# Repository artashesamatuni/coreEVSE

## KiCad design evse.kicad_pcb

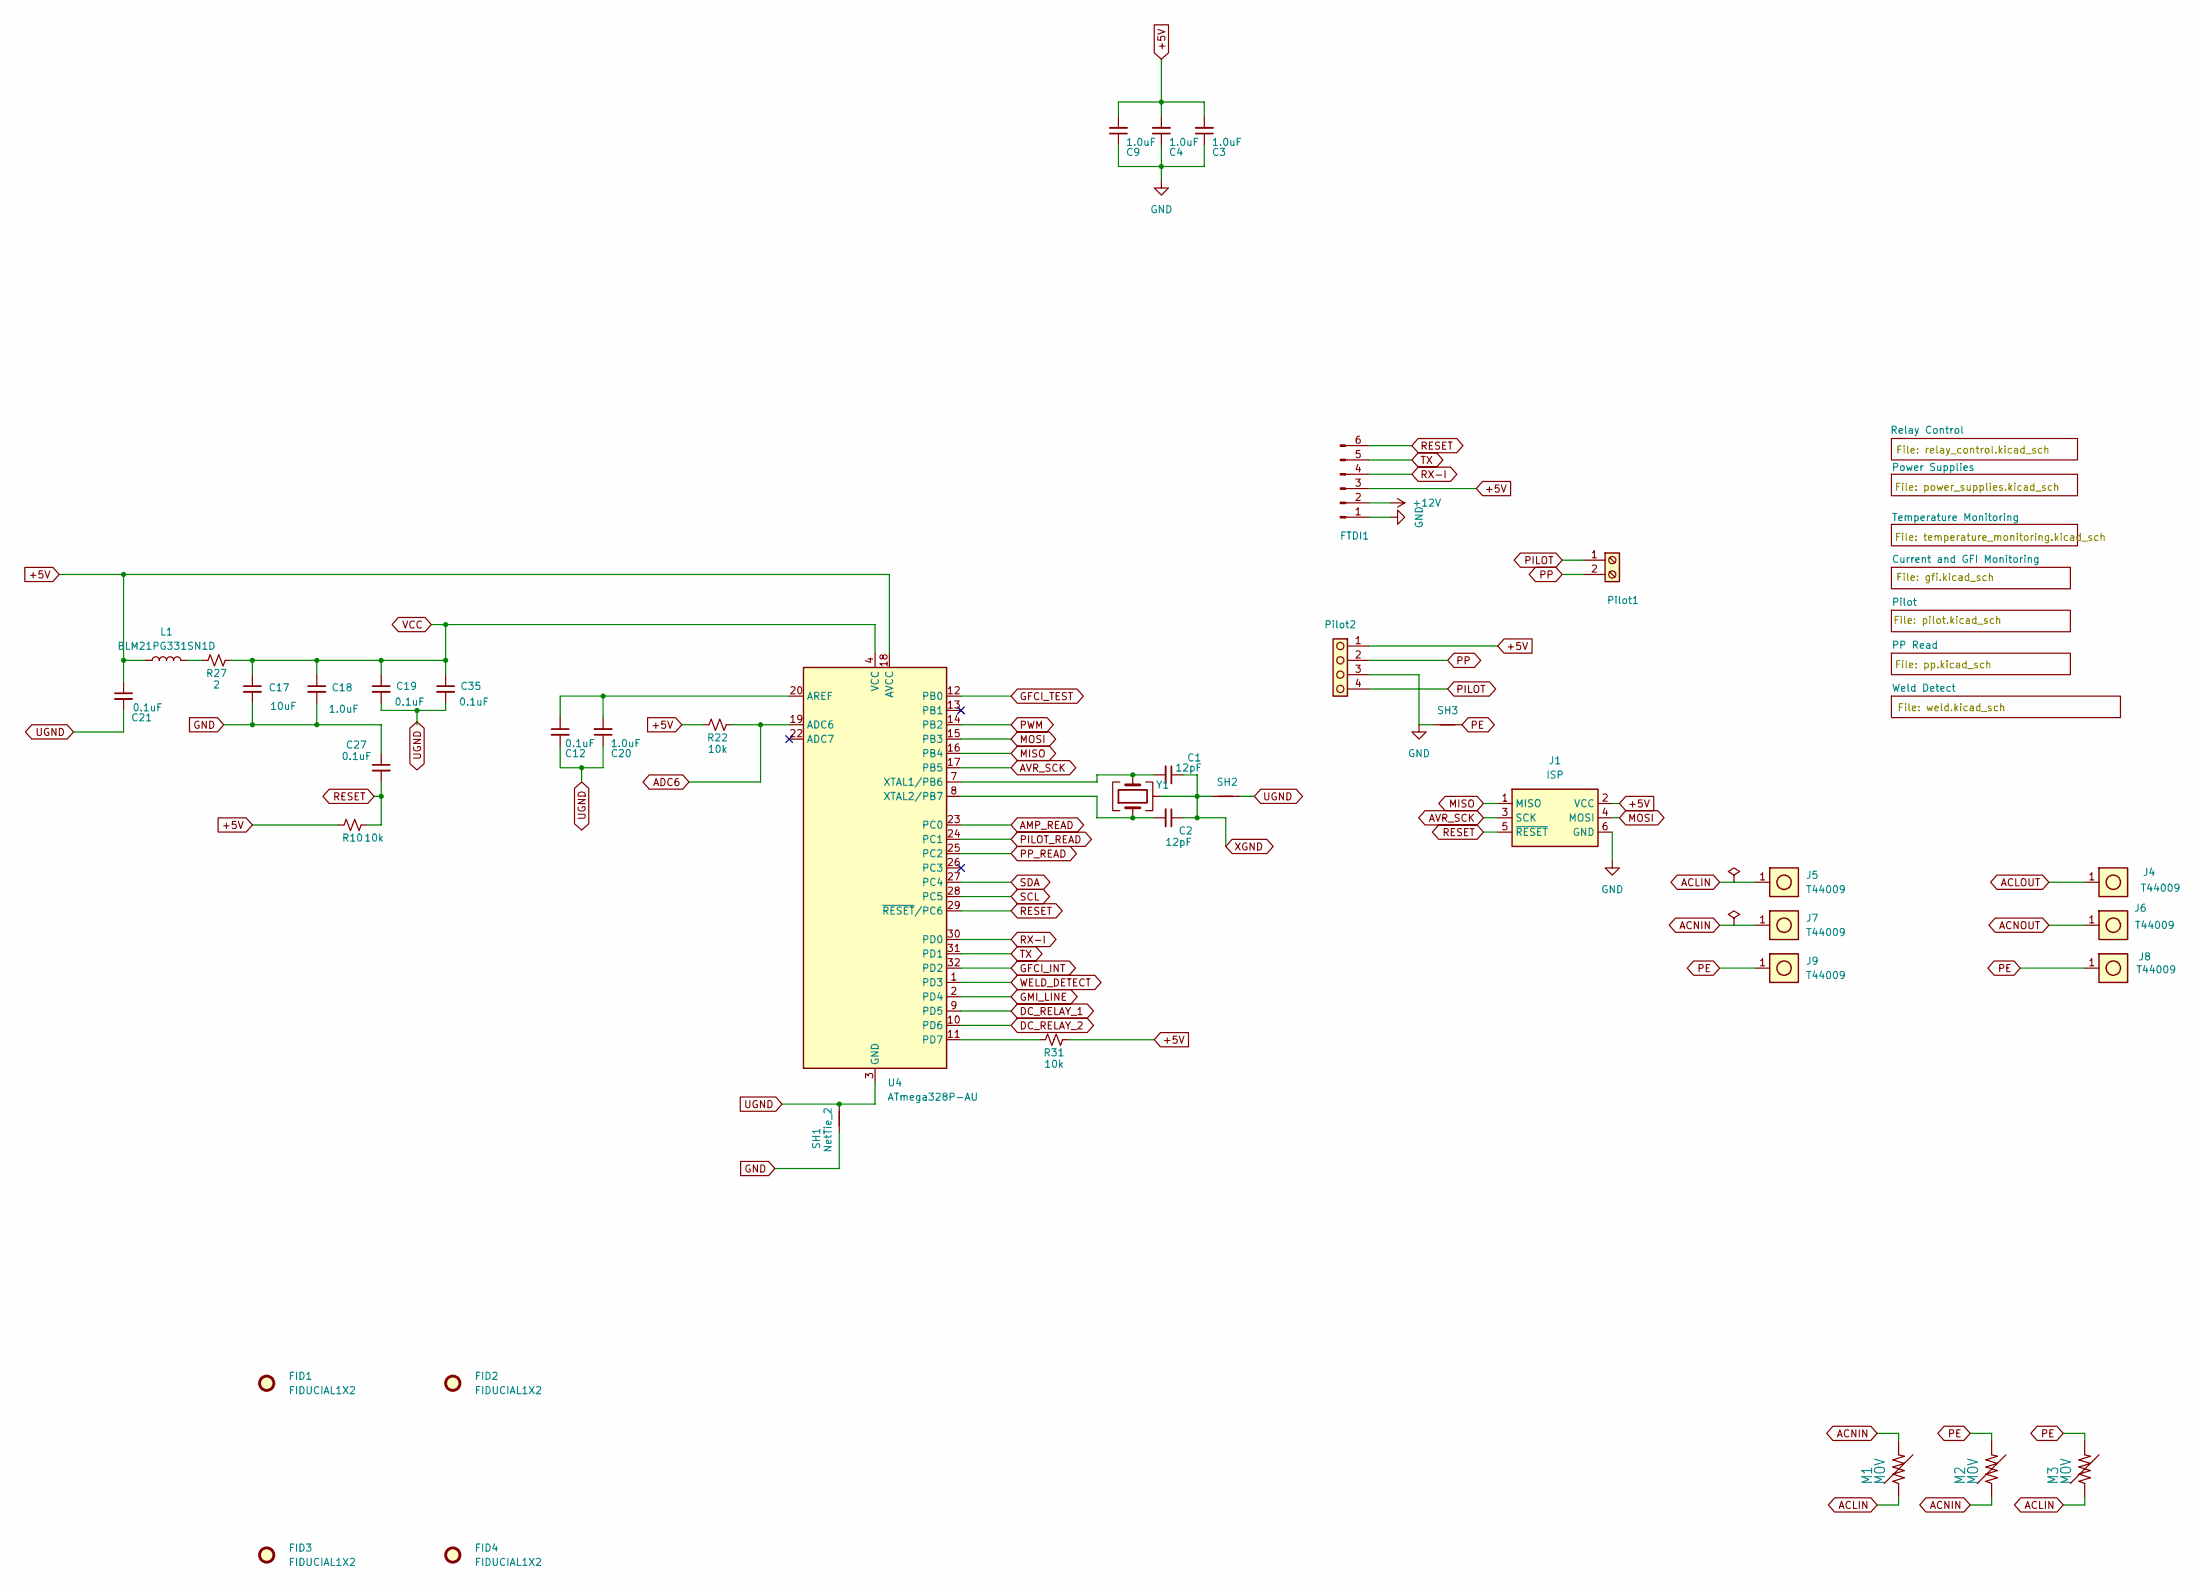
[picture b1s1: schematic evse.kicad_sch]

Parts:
C1, C2: 12pF; C_0402_1005Metric; Voltage 50V; Tolerance 2%; LCSC C696888
C3, C4, C9, C20: 1.0uF; C_0805_2012Metric; Voltage 25V; Tolerance 10%; LCSC C3848979
C12, C19, C21, C27: 0.1uF; C_0805_2012Metric; Voltage 25V; Tolerance 10%; LCSC C129641
C17: 10uF; C_0603_1608Metric_Polar; Voltage 10V; Tolerance 20%
C18: 1.0uF; C_0201_0603Metric; Voltage 25V; Tolerance 10%
C35: 0.1uF; C_0402_1005Metric; Voltage 25V; Tolerance 10%; LCSC C169842
FID1, FID2, FID3, FID4: FIDUCIAL1X2; Fiducial_1mm_Mask2mm
FTDI1: Conn_01x06_Pin; FTDI_JST_PH_1x06_P2.00mm
J1: ISP; AVR_ISP_2x03_P2.54mm
J4, J5, J6, J7, J8, J9: T44009; Terminal_T44009_M4
L1: BLM21PG331SN1D; L_0805_2012Metric; LCSC C74764
M1, M2, M3: MOV
Pilot1: KF128-2.54-2P; TerminalBlock_KF128-2.54-2P; LCSC C474920
Pilot2: KF128-2.54-4P; TerminalBlock_KF128-2.54-4P; LCSC C474922
R10, R22, R31: 10k; R_0805_2012Metric; LCSC C7337170
R27: 2; R_0805_2012Metric; LCSC C2078467
SH1, SH2, SH3: NetTie_2; NetTie-2_SMD_Pad0.5mm
U4: ATmega328P-AU; TQFP-32_7x7mm_P0.8mm; Operating Voltage Range 1.8V~5.5V; Low Voltage Detection T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 1.8V~5.5V; Part ATMEGA328P-AU; LCSC C14877
Y1: FA-238A 16MHz CL=8pF; Crystal_SMD_SeikoEpson_TSX3225-4Pin_3.2x2.5mm

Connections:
+5V: C3.2, C4.2, C9.2, C21.1, FTDI1.3, J1.2 (VCC), L1.1, Pilot2.1, R10.1, R22.1, R31.2, U4.18 (AVCC); also elsewhere on the board
+12V: FTDI1.2; also elsewhere on the board
ACLIN: J5.1 (Terminal_1), M1.P$1 (1), M3.P$1 (1); also elsewhere on the board
ACNIN: J7.1 (Terminal_1), M1.P$2 (2), M2.P$1 (1); also elsewhere on the board
AC_L_OUT: J4.1 (Terminal_1); also elsewhere on the board
AC_N_OUT: J6.1 (Terminal_1); also elsewhere on the board
ADC6: R22.2, U4.19 (ADC6)
AMP_READ: U4.23 (PC0); also elsewhere on the board
AVR_SCK: J1.3 (SCK), U4.17 (PB5)
DC_RELAY_1: U4.9 (PD5); also elsewhere on the board
DC_RELAY_2: U4.10 (PD6); also elsewhere on the board
GFCI_INT: U4.32 (PD2); also elsewhere on the board
GFCI_TEST: U4.12 (PB0); also elsewhere on the board
GMI_LINE: U4.2 (PD4); also elsewhere on the board
GND: C3.1, C4.1, C9.1, C17.2, C18.2, C27.1, FTDI1.1, J1.6 (GND), Pilot2.3, SH1.1, SH3.1; also elsewhere on the board
MISO: J1.1 (MISO), U4.16 (PB4)
MOSI: J1.4 (MOSI), U4.15 (PB3)
unnamed: L1.2, R27.1
unnamed: R31.1, U4.11 (PD7)
unnamed: C1.2, U4.7 (XTAL1/PB6), Y1.3
unnamed: C2.2, U4.8 (XTAL2/PB7), Y1.1
PE: J8.1 (Terminal_1), J9.1 (Terminal_1), M2.P$2 (2), M3.P$2 (2), SH3.2; also elsewhere on the board
PILOT: Pilot1.1, Pilot2.4; also elsewhere on the board
PILOT_READ: U4.24 (PC1); also elsewhere on the board
PP: Pilot1.2, Pilot2.2; also elsewhere on the board
PP_READ: U4.25 (PC2); also elsewhere on the board
PWM: U4.14 (PB2); also elsewhere on the board
RESET: C27.2, FTDI1.6, J1.5 (~RESET), R10.2, U4.29 (~RESET/PC6)
RX-I: FTDI1.4, U4.30 (PD0)
SCL: U4.28 (PC5); also elsewhere on the board
SDA: U4.27 (PC4); also elsewhere on the board
TX: FTDI1.5, U4.31 (PD1)
VCC: C17.1, C18.1, C19.1, C35.1, R27.2, U4.4 (VCC), U4.6 (VCC)
WELD_DETECT: U4.1 (PD3); also elsewhere on the board
XGND: C1.1, C2.1, SH2.2, Y1.2 (G), Y1.4 (G)

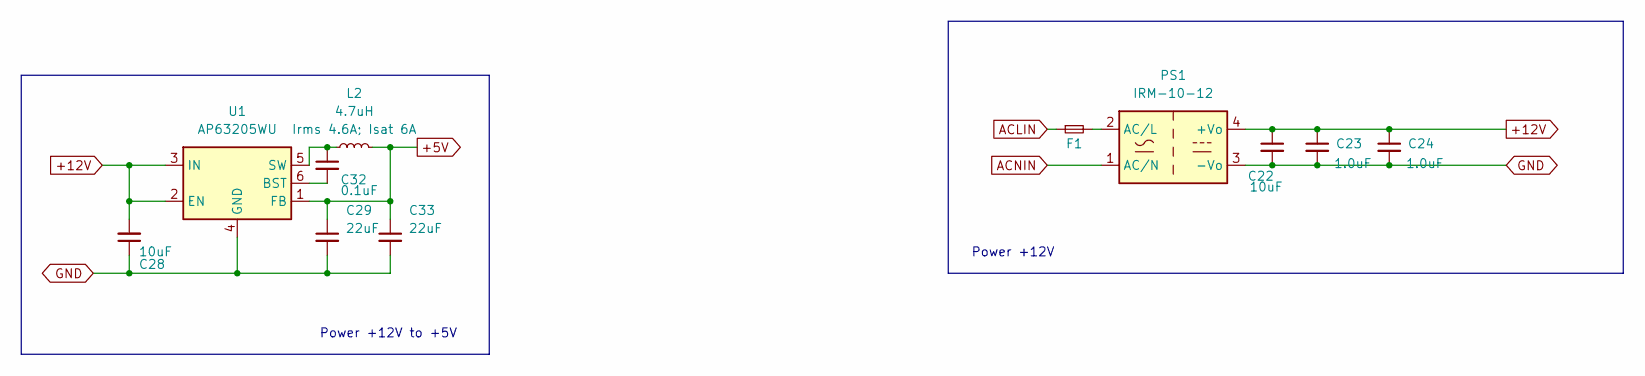
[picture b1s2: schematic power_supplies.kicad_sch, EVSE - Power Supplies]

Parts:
C22: 10uF; C_1206_3216Metric; Voltage 25V; Tolerance 10%; LCSC C380364
C23, C24: 1.0uF; C_0805_2012Metric; Voltage 25V; Tolerance 10%; LCSC C3848979
C28: 10uF; C_0805_2012Metric; Voltage 25V; Tolerance 10%; LCSC C5448891
C29, C33: 22uF; C_0805_2012Metric; Voltage 16V; Tolerance 20%; LCSC C380339
C32: 0.1uF; C_0805_2012Metric; Voltage 16V; Tolerance 10%; LCSC C129641
F1: 1.6A 250VAC slow-blow; BELFUSE1A
L2: 4.7uH; L_Bourns_SRP5030T; LCSC C2045677
PS1: IRM-10-12; Converter_ACDC_MeanWell_IRM-10-12_THT
U1: AP63205WU; TSOT-23-6

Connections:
+5V: C29.1, C33.1, L2.2, U1.1 (FB); also elsewhere on the board
+12V: C22.1, C23.1, C24.1, C28.2, PS1.4 (+Vo), U1.2 (EN), U1.3 (IN); also elsewhere on the board
ACLIN: F1.1; also elsewhere on the board
ACNIN: PS1.1 (AC/N); also elsewhere on the board
GND: C22.2, C23.2, C24.2, C28.1, C29.2, C33.2, PS1.3 (-Vo), U1.4 (GND); also elsewhere on the board
unnamed: F1.2, PS1.2 (AC/L)
unnamed: C32.2, U1.6 (BST)
unnamed: C32.1, L2.1, U1.5 (SW)

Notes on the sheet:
Power +12V
Power +12V to +5V

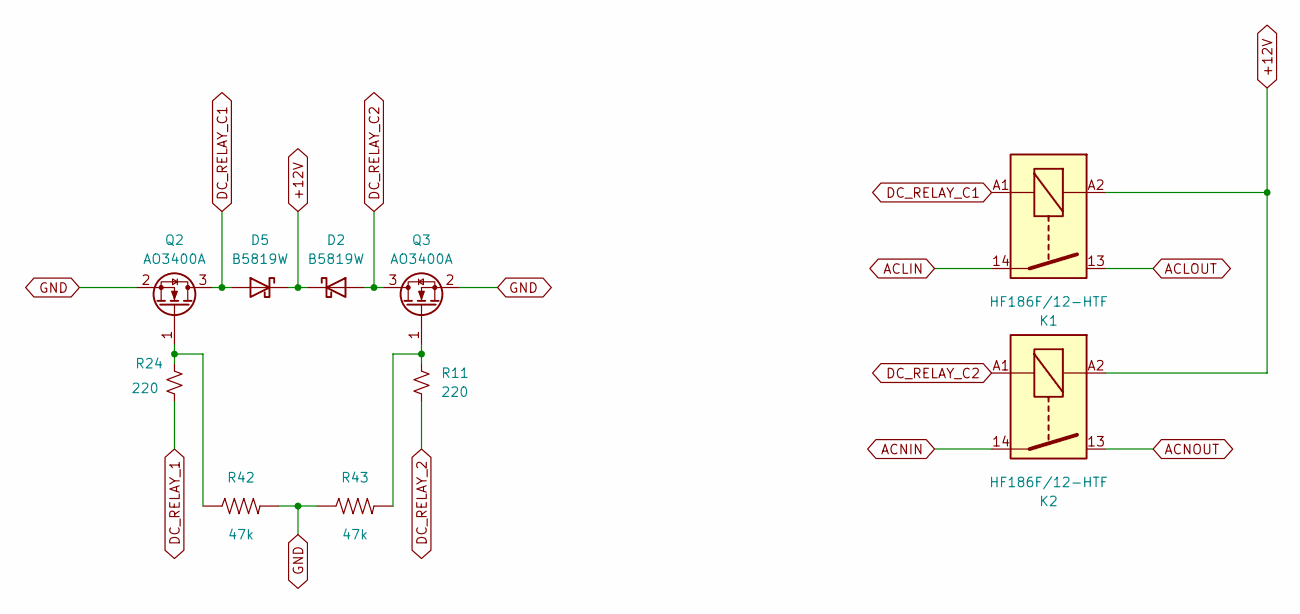
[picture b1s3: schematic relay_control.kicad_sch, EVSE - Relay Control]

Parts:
D2, D5: B5819W; D_SOD-123; LCSC C64885
K1, K2: HF186F/12-HTF; Relay_Hongfa_HF186F_PushIn; LCSC C6388924
Q2, Q3: AO3400A; SOT-23; LCSC C2803353
R11, R24: 220; R_0805_2012Metric; LCSC C17557
R42, R43: 47k; R_0805_2012Metric; LCSC C4238470

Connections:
+12V: D2.1 (K), D5.1 (K), K1.A2, K2.A2; also elsewhere on the board
ACLIN: K1.14; also elsewhere on the board
ACNIN: K2.14; also elsewhere on the board
AC_L_OUT: K1.13; also elsewhere on the board
AC_N_OUT: K2.13; also elsewhere on the board
DC_RELAY_1: R24.2; also elsewhere on the board
DC_RELAY_2: R11.1; also elsewhere on the board
DC_RELAY_C1: D5.2 (A), K1.A1, Q2.3 (D)
DC_RELAY_C2: D2.2 (A), K2.A1, Q3.3 (D)
GND: Q2.2 (S), Q3.2 (S), R42.2, R43.1; also elsewhere on the board
unnamed: Q2.1 (G), R24.1, R42.1
unnamed: Q3.1 (G), R11.2, R43.2

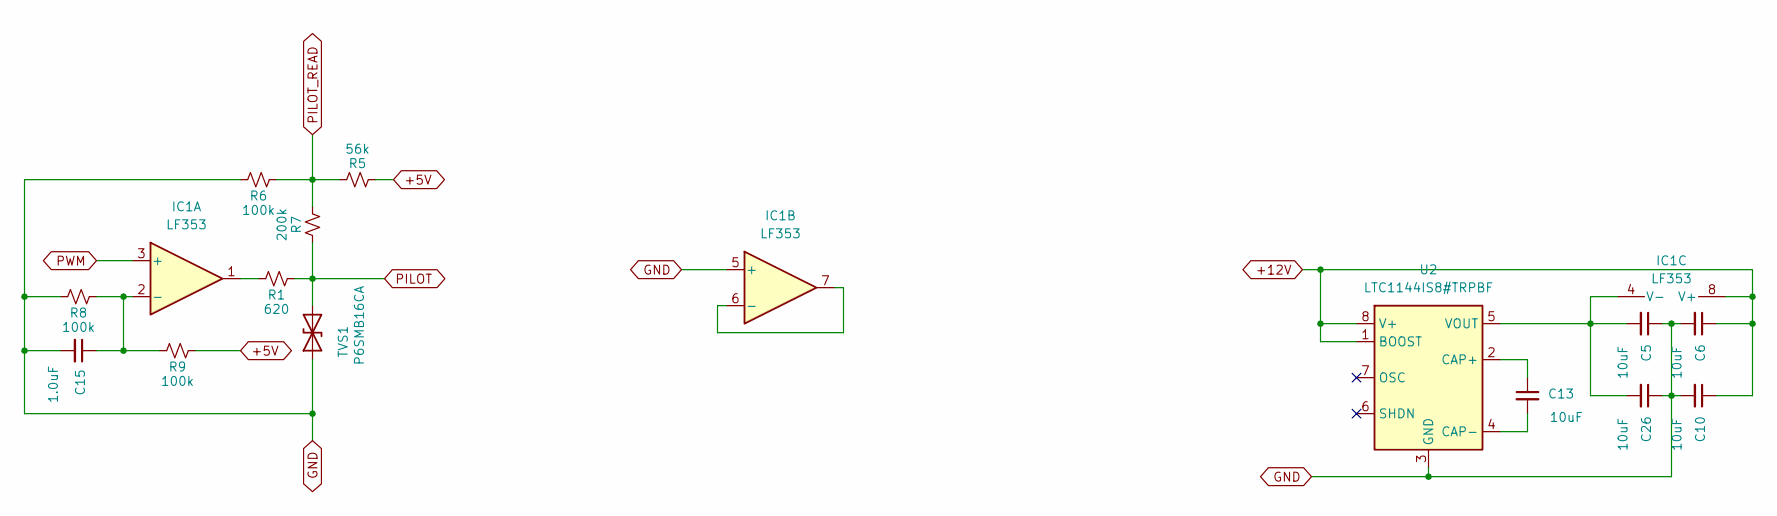
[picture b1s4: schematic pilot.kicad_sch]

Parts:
C5, C6, C10, C13, C26: 10uF; C_1210_3225Metric; Voltage 50V; Tolerance 10%; LCSC C17702790
C15: 1.0uF; C_0805_2012Metric; Voltage 25V; Tolerance 10%; LCSC C3848979
IC1: LF353; SOIC-8_3.9x4.9mm_P1.27mm
R1: 620; R_0805_2012Metric; LCSC C2907279
R5: 56k; R_0805_2012Metric; LCSC C4163131
R6, R8, R9: 100k; R_0805_2012Metric; LCSC C465471
R7: 200k; R_0805_2012Metric; LCSC C228624
TVS1: P6SMB16CA; SMB
U2: LTC1144IS8#TRPBF; SOIC-8_3.9x4.9mm_P1.27mm

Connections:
+5V: R5.1, R9.2; also elsewhere on the board
+12V: C6.1, C10.1, IC1.8 (V+), U2.1 (BOOST), U2.8 (V+); also elsewhere on the board
GND: C5.1, C6.2, C10.2, C15.2, C26.1, IC1.5 (+), R6.1, R8.1, TVS1.1 (A1), U2.3 (GND); also elsewhere on the board
unnamed: IC1.1, R1.1
unnamed: C15.1, IC1.2 (-), R8.2, R9.1
unnamed: IC1.6 (-), IC1.7
unnamed: C5.2, C26.2, IC1.4 (V-), U2.5 (VOUT)
unnamed: C13.1, U2.2 (CAP+)
unnamed: C13.2, U2.4 (CAP-)
PILOT: R1.2, R7.2, TVS1.2 (A2); also elsewhere on the board
PILOT_READ: R5.2, R6.2, R7.1; also elsewhere on the board
PWM: IC1.3 (+); also elsewhere on the board

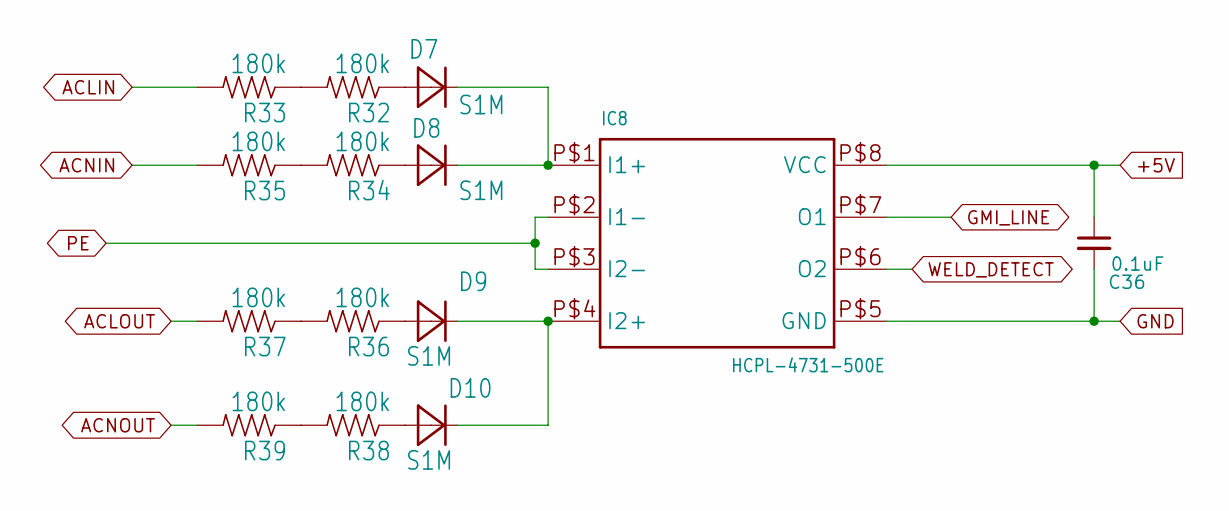
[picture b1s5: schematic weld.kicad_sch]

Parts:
C36: 0.1uF; C_0805_2012Metric; Voltage 25V; Tolerance 10%; LCSC C129641
D7, D8, D9, D10: S1M; SMA_AC
IC8: HCPL-4731-500E; SIL8-2; LCSC C692052
R32, R33, R34, R35, R36, R37, R38, R39: 180k; R_2512_6332Metric; Tolerance 1%; MPN HV733ATTE1803F

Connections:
+5V: C36.1, IC8.P$8 (VCC); also elsewhere on the board
ACLIN: R33.2; also elsewhere on the board
ACNIN: R35.2; also elsewhere on the board
AC_L_OUT: R37.2; also elsewhere on the board
AC_N_OUT: R39.2; also elsewhere on the board
GMI_LINE: IC8.P$7 (O1); also elsewhere on the board
GND: C36.2, IC8.P$5 (GND); also elsewhere on the board
unnamed: D7.A, R32.1
unnamed: D8.A, R34.1
unnamed: D9.A, R36.1
unnamed: D10.A, R38.1
unnamed: D7.C, D8.C, IC8.P$1 (I1+)
unnamed: D9.C, D10.C, IC8.P$4 (I2+)
unnamed: R32.2, R33.1
unnamed: R34.2, R35.1
unnamed: R36.2, R37.1
unnamed: R38.2, R39.1
PE: IC8.P$2 (I1-), IC8.P$3 (I2-); also elsewhere on the board
WELD_DETECT: IC8.P$6 (O2); also elsewhere on the board

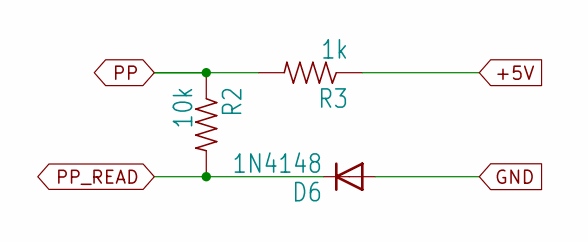
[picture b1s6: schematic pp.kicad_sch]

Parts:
D6: 1N4148; SOD-123_AC
R2: 10k; R_0805_2012Metric; LCSC C7337170
R3: 1k; R_0805_2012Metric; LCSC C2889437

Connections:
+5V: R3.1; also elsewhere on the board
GND: D6.A; also elsewhere on the board
PP: R2.1, R3.2; also elsewhere on the board
PP_READ: D6.C, R2.2; also elsewhere on the board

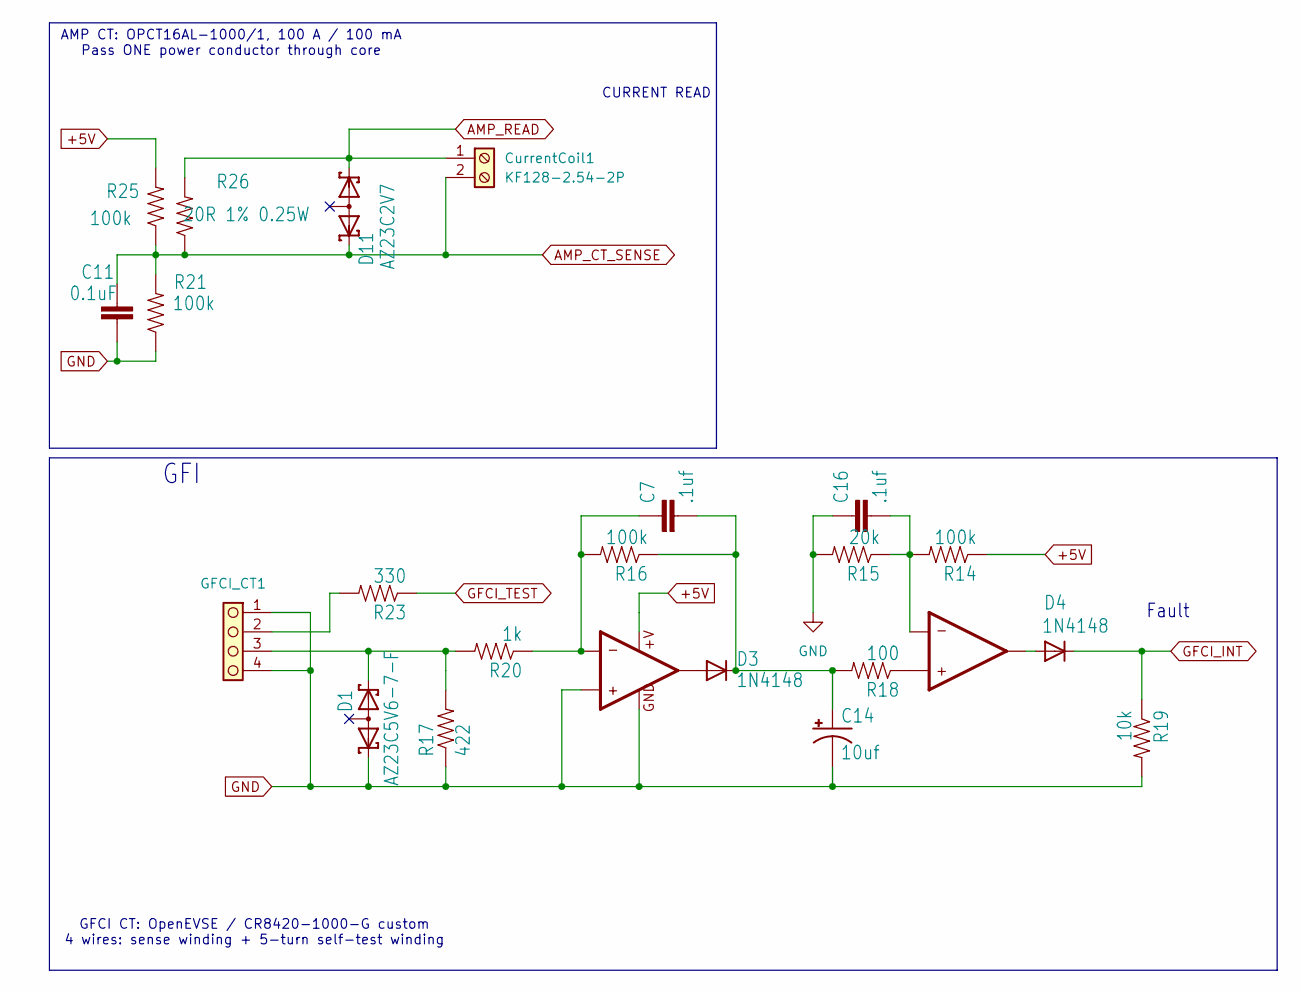
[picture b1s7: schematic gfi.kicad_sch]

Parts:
C7, C16: .1uf; C_0805_2012Metric; LCSC C129641
C11: 0.1uF; C_0805_2012Metric; LCSC C129641
C14: 10uf; C_1206_3216Metric_AC
CurrentCoil1: KF128-2.54-2P; TerminalBlock_KF128-2.54-2P; LCSC C474920
D1: AZ23C5V6-7-F; SOT-23
D3, D4: 1N4148; SOD-123_AC
D11: AZ23C2V7; SOT23-3
GFCI_CT1: KF128-2.54-4P; TerminalBlock_KF128-2.54-4P; LCSC C474922
IC3: LM358; SOIC-8_3.9x4.9mm_P1.27mm; LCSC C5423
R14, R16, R21, R25: 100k; R_0805_2012Metric; LCSC C465471
R15: 20k; R_0805_2012Metric; LCSC C114566
R17: 422; R_0805_2012Metric; LCSC C5635137
R18: 100; R_0805_2012Metric; LCSC C2889469
R19: 10k; R_0805_2012Metric; LCSC C7337170
R20: 1k; R_0805_2012Metric; LCSC C2889437
R23: 330; R_0805_2012Metric; LCSC C2889518
R26: 20R 1% 0.25W; R_0805_2012Metric; LCSC C363248

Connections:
+5V: IC3.8 (+V), R14.1, R25.2; also elsewhere on the board
AMP_CT_SENSE: C11.1, CurrentCoil1.2, D11.1 (K1), R21.2, R25.1, R26.1
AMP_READ: CurrentCoil1.1, D11.2 (K2), R26.2; also elsewhere on the board
GFCI_INT: D4.C, R19.1; also elsewhere on the board
GFCI_TEST: R23.1; also elsewhere on the board
GND: C11.2, C14.C (-), C16.1, D1.1 (K1), GFCI_CT1.1, GFCI_CT1.4, IC3.3 (+IN1), IC3.4 (GND), R15.2, R17.1, R19.2, R21.1; also elsewhere on the board
unnamed: C7.2, C14.A (+), D3.C, R16.1, R18.2
unnamed: D1.2 (K2), GFCI_CT1.3, R17.2, R20.2
unnamed: GFCI_CT1.2, R23.2
unnamed: C7.1, IC3.2 (-IN1), R16.2, R20.1
unnamed: D3.A, IC3.1 (OUT1)
unnamed: IC3.5 (+IN2), R18.1
unnamed: C16.2, IC3.6 (-IN2), R14.2, R15.1
unnamed: D4.A, IC3.7 (OUT2)

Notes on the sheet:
CURRENT READ
AMP CT: OPCT16AL-1000/1, 100 A / 100 mA Pass ONE power conductor through core
Fault
GFI
GFCI CT: OpenEVSE / CR8420-1000-G custom 4 wires: sense winding + 5-turn self-test winding

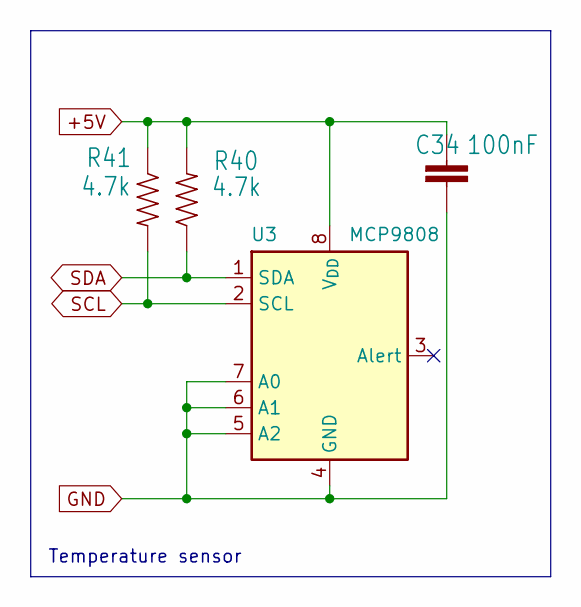
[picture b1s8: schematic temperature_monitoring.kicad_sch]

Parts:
C34: 100nF; C_0805_2012Metric; LCSC C129641
R40, R41: 4.7k; R_0805_2012Metric; LCSC C140869
U3: MCP9808; MSOP-8_3x3mm_P0.65mm

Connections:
+5V: C34.1, R40.2, R41.1, U3.8 (V_{DD}); also elsewhere on the board
GND: C34.2, U3.4 (GND), U3.5 (A2), U3.6 (A1), U3.7 (A0); also elsewhere on the board
SCL: R41.2, U3.2 (SCL); also elsewhere on the board
SDA: R40.1, U3.1 (SDA); also elsewhere on the board

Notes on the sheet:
Temperature sensor

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
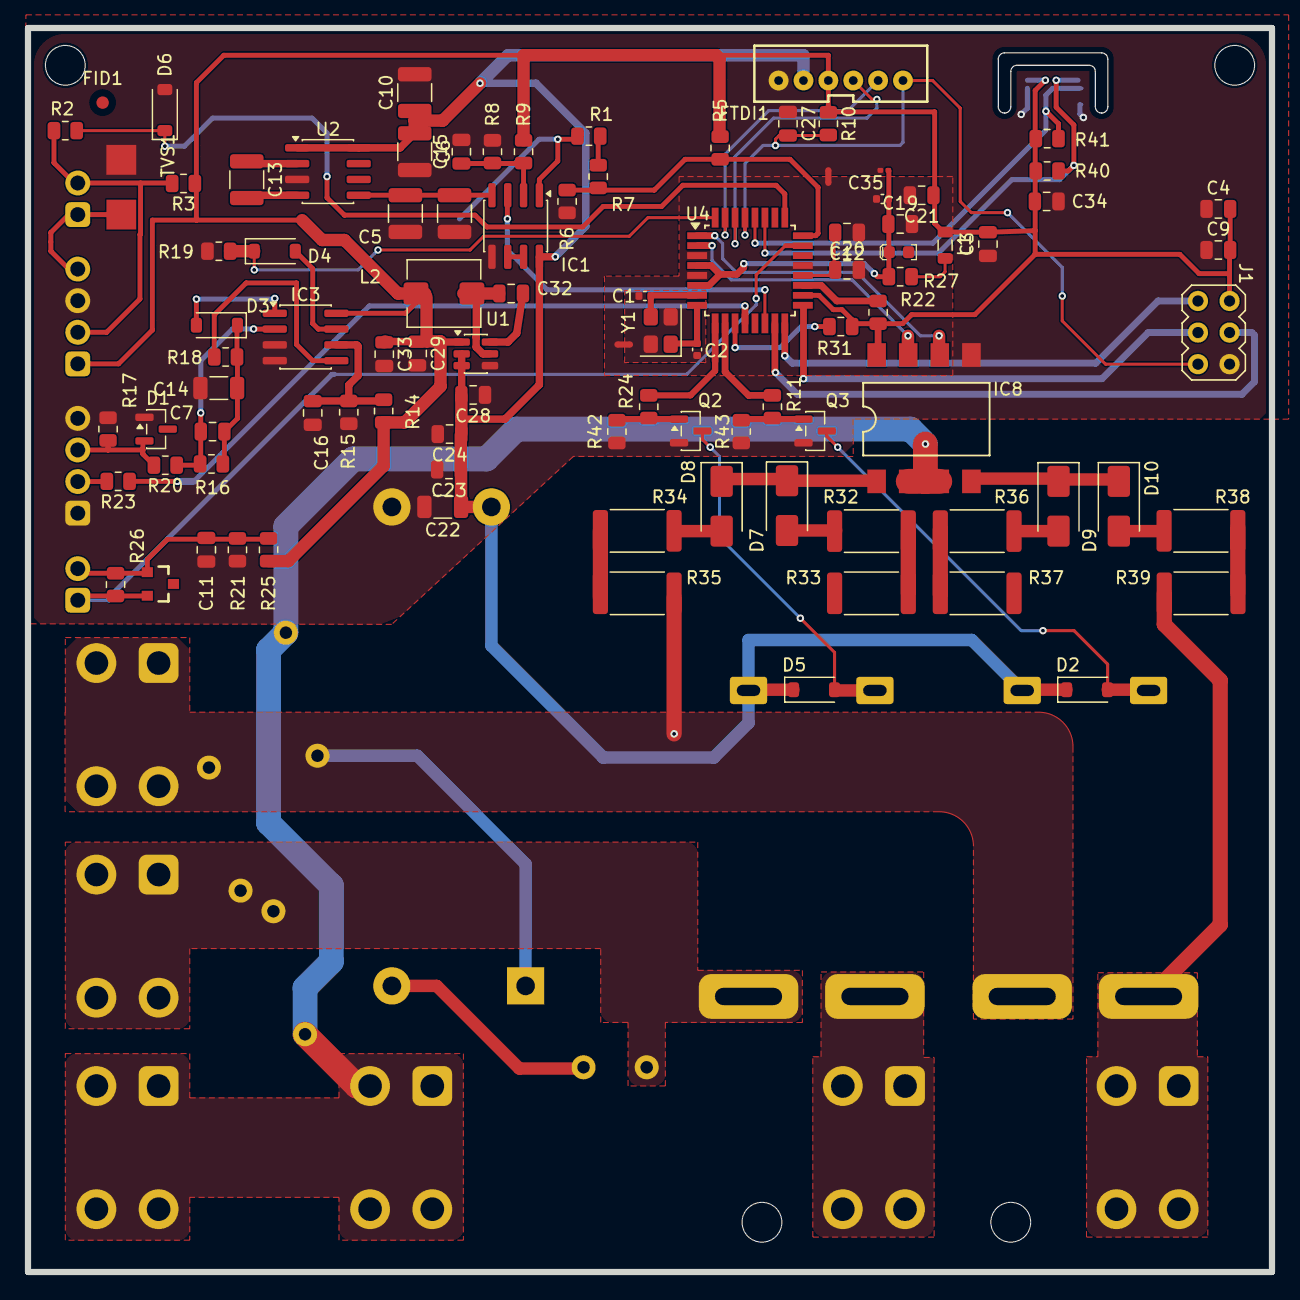
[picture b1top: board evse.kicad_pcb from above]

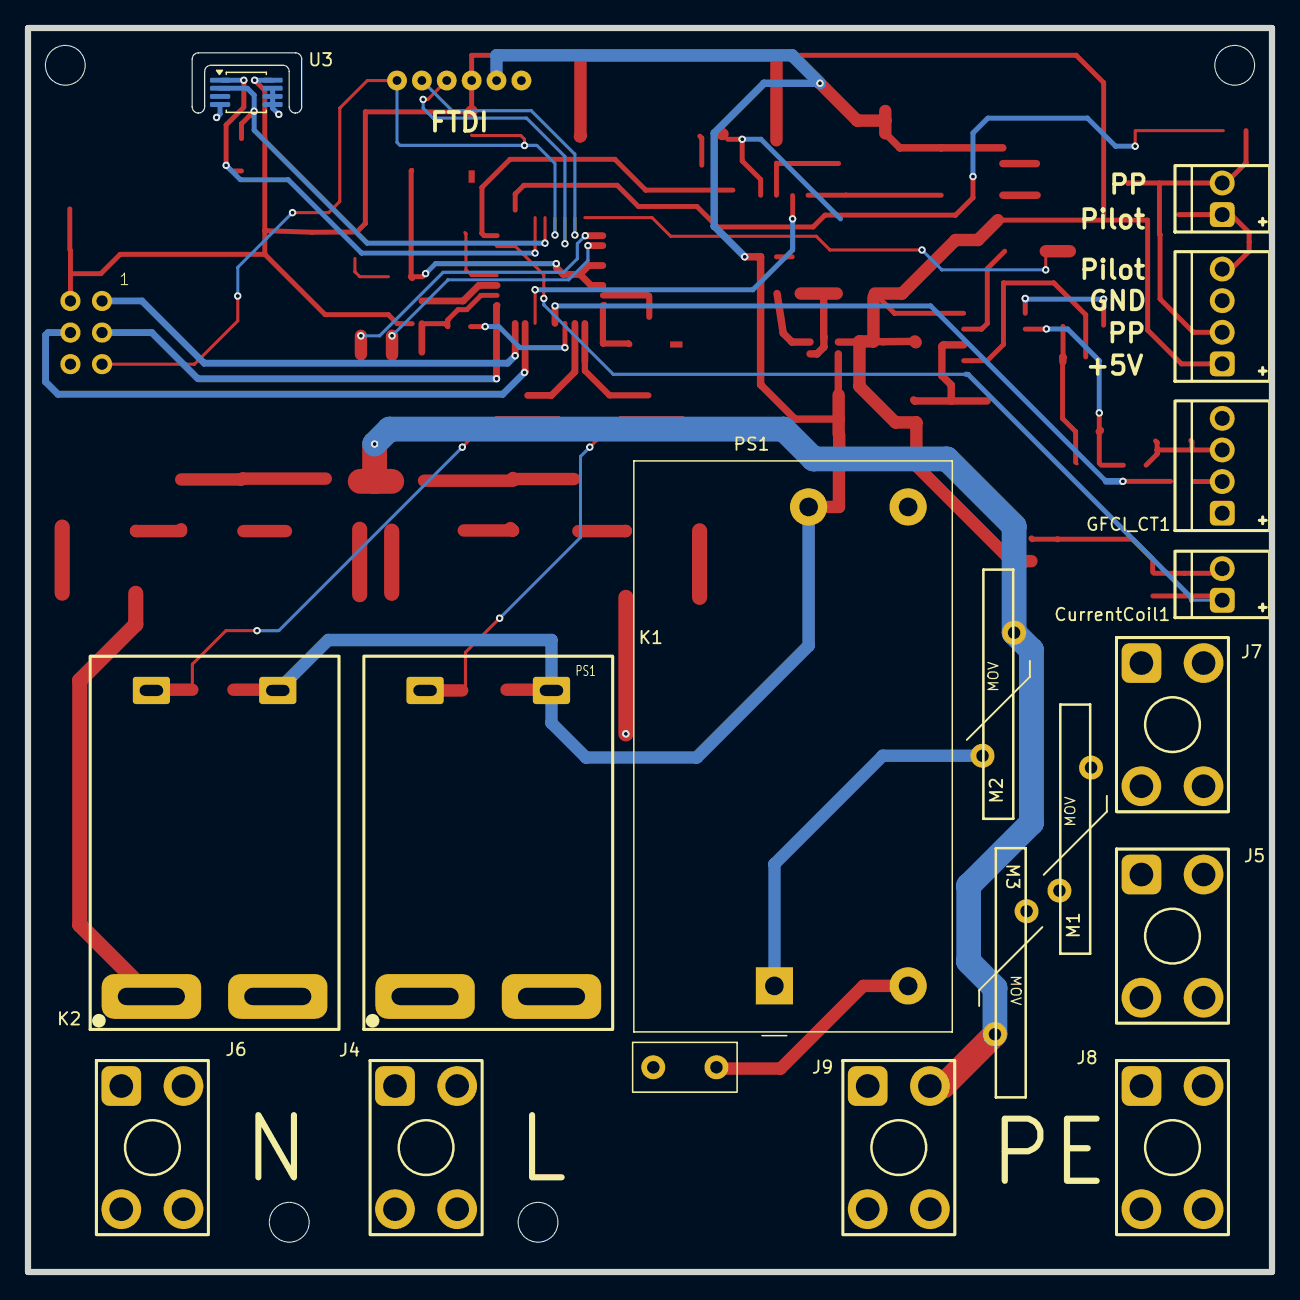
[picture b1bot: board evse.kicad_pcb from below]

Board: 2 copper layers, 100.0 x 100.0 mm, 117 parts (20 on the bottom side), 69 nets.

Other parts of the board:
UNK_HOLE_1, UNK_HOLE_1#2, UNK_HOLE_1#3: dummyfp1

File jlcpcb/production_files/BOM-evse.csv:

Comment,Designator,Footprint,LCSC,Quantity
ATmega328P-AU,U4,TQFP-32_7x7mm_P0.8mm,C14877,1
KF128-2.54-2P,"CurrentCoil1,Pilot1",TerminalBlock_KF128-2.54-2P,C474920,2
KF128-2.54-4P,"GFCI_CT1,Pilot2",TerminalBlock_KF128-2.54-4P,C474922,2
TC1044S,U2,SOIC-8_3.9x4.9mm_P1.27mm,,1
AP63205WU,U1,TSOT-23-6,,1
P6SMB16CA,TVS1,SMB,,1
4.7k,R41,R_0805_2012Metric,,1
4.7k,R40,R_0805_2012Metric,,1
180k,R39,R_1210_3225Metric,,1
180k,R38,R_1210_3225Metric,,1
180k,R37,R_1210_3225Metric,,1
180k,R36,R_1210_3225Metric,,1
180k,R35,R_1210_3225Metric,,1
180k,R34,R_1210_3225Metric,,1
180k,R33,R_1210_3225Metric,,1
180k,R32,R_1210_3225Metric,,1
10k,R31,R_0805_2012Metric,,1
2,R27,R_0805_2012Metric,,1
20R 1% 0.25W,R26,R_0805_2012Metric,,1
100k,R25,R_0805_2012Metric,,1
220,R24,R_0805_2012Metric,,1
330,R23,R_0805_2012Metric,,1
10k,R22,R_0805_2012Metric,,1
100k,R21,R_0805_2012Metric,,1
1k,R20,R_0805_2012Metric,,1
10k,R19,R_0805_2012Metric,,1
100,R18,R_0805_2012Metric,,1
422,R17,R_0805_2012Metric,,1
100k,R16,R_0805_2012Metric,,1
20k,R15,R_0805_2012Metric,,1
100k,R14,R_0805_2012Metric,,1
220,R11,R_0805_2012Metric,,1
10k,R10,R_0805_2012Metric,,1
100k,R9,R_0805_2012Metric,,1
100k,R8,R_0805_2012Metric,,1
200k,R7,R_0805_2012Metric,,1
100k,R6,R_0805_2012Metric,,1
56k,R5,R_0805_2012Metric,,1
1k,R3,R_0805_2012Metric,,1
10k,R2,R_0805_2012Metric,,1
620,R1,R_0805_2012Metric,,1
MMBT2222A,Q3,SOT-23,,1
MMBT2222A,Q2,SOT-23,,1
MOV,M3,MOV,,1
MOV,M2,MOV,,1
MOV,M1,MOV,,1
4.7uH,L2,NR5040,,1
HCPL-2731S,IC8,SIL8-2,,1
LM358,IC3,SOIC-8_3.9x4.9mm_P1.27mm,,1
LF353,IC1,SOIC-8_3.9x4.9mm_P1.27mm,,1
1N4004,D10,SMA_AC,,1
1N4004,D9,SMA_AC,,1
1N4004,D8,SMA_AC,,1
1N4004,D7,SMA_AC,,1
1N4148,D6,SOD-123_AC,,1
SS14,D5,D_SOD-123,,1
1N4148,D4,SOD-123_AC,,1
1N4148,D3,SOD-123_AC,,1
SS14,D2,D_SOD-123,,1
AZ23C5V6-7-F,D1,SOT-23,,1
0.1uF,C35,C_0402_1005Metric,,1
100nF,C34,C_0805_2012Metric,,1
0.1uF,C32,C_0805_2012Metric,,1
10uF,C26,C_0805_2012Metric,,1
10uF,C22,C_1206_3216Metric,,1
.1uf,C16,C_0805_2012Metric,,1
10uf,C14,C_1206_3216Metric_AC,,1
10uF,C13,C_0805_2012Metric,,1
0.1uF,C11,C_0805_2012Metric,,1
10uF,C10,C_0805_2012Metric,,1
.1uf,C7,C_0805_2012Metric,,1
10uF,C6,C_0805_2012Metric,,1
10uF,C5,C_0805_2012Metric,,1
22pF,C2,C_0805,,1
22pF,C1,C_0805,,1
FIDUCIAL1X2.5,FID4,FIDUCIAL-1X2.5,,1
,UNK_HOLE_1,dummyfp1,,1
M01PTH,G2,1X01,,1
T44009,J4,Terminal_T44009_M4,,1
1.6A 250VAC slow-blow,F1,BELFUSE1A,,1
T44009,J5,Terminal_T44009_M4,,1
MCP9808,U3,MSOP-8_3x3mm_P0.65mm,,1
ISP,J1,AVR_ISP_2x03_P2.54mm,,1
HF186F/12-HCTF,K2,Relay_Hongfa_HF186F_PushIn,,1
T44009,J7,Terminal_T44009_M4,,1
T44009,J6,Terminal_T44009_M4,,1
T44009,J8,Terminal_T44009_M4,,1
T44009,J9,Terminal_T44009_M4,,1
HF186F/12-HCTF,K1,Relay_Hongfa_HF186F_PushIn,,1
Conn_01x06_Pin,FTDI1,FTDI_JST_PH_1x06_P2.00mm,,1
IRM-10-12,PS1,Converter_ACDC_MeanWell_IRM-10-12_THT,,1
16MHz,Y1,Crystal_SMD_3.2x2.5mm,,1
BLM21PG331SN1D,L1,0805,,1
AZ23C2V7,D11,SOT23-3,,1
22uF,C33,C_0805_2012Metric,,1
22uF,C29,C_0805_2012Metric,,1
10uF,C28,C_0805_2012Metric,,1
0.1uF,C27,C_0805_2012Metric,,1
1.0uF,C24,C_0805_2012Metric,,1
1.0uF,C23,C_0805_2012Metric,,1
0.1uF,C21,C_0805_2012Metric,,1
1.0uF,C20,C_0805_2012Metric,,1
0.1uF,C19,C_0805_2012Metric,,1
1.0uF,C18,C_0201_0603Metric,,1
10uF,C17,C_0603_1608Metric_Polar,,1
1.0uF,C15,C_0805_2012Metric,,1
0.1uF,C12,C_0805_2012Metric,,1
1.0uF,C9,C_0805_2012Metric,,1
1.0uF,C4,C_0805_2012Metric,,1
1.0uF,C3,C_0805_2012Metric,,1
